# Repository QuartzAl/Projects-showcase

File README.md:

<!-- PROJECT LOGO -->
<br />
<div align="center">

<h3 align="center">Projects World!</h3>

Main repository where I keep all of my project showcases related to Electrical Engineering
These include PCB designs, electronic circuits, code snippets, and more. The directories in this repository refer to individual projects that were completed that I think do not need their own github repository

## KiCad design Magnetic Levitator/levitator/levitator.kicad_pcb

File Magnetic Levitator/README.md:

# Magnetic Levitator

A simple magnetic levitator I made with an ON-OFF controller, the system kind of Proportional controller's itself because of the inductive effect of the coil, hence why not need to use an actual proportional controller. The coil had to be wound with care as inalignment of the coil would reduce it's magnetic strength, the object to be lifted in this levitator has to also be a magnet in order to give proper feedback to the SS49E sensor. The frame of the magnetic levitator I built from several pieces of cut cardboard and hotglue, enough to hold the coil and circuit.

## Components

The main components used for the magnetic levitator is as follows:
- 2 ounces of 0.5mm diameter copper wire (around 120 Meters)
- SS49E linear hall effect sensor
- an MP1584 step down converter
- LM358 OpAmp
- IRLZ44n
- 1N5819; and
- some resistors and capacitors

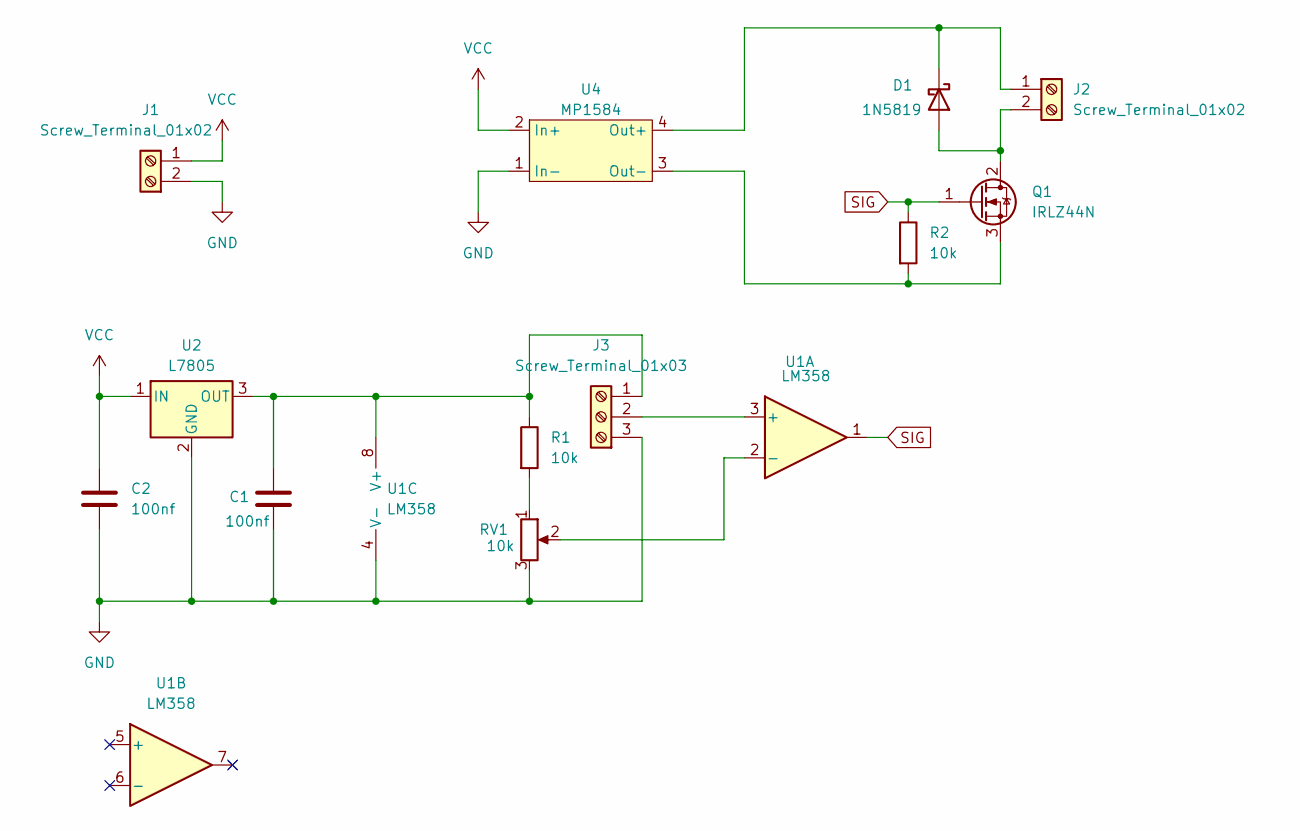
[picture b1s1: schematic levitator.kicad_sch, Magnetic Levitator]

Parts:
C1, C2: 100nf; C_1206_3216Metric_Pad1.33x1.80mm_HandSolder
D1: 1N5819; D_DO-41_SOD81_P10.16mm_Horizontal
J1: Screw_Terminal_01x02; Screw terminal
J2: Screw_Terminal_01x02; JST_EH_B2B-EH-A_1x02_P2.50mm_Vertical
J3: Screw_Terminal_01x03; JST_EH_B3B-EH-A_1x03_P2.50mm_Vertical
Q1: IRLZ44N; TO-220-3_Vertical
R1, R2: 10k; R_0805_2012Metric_Pad1.20x1.40mm_HandSolder
RV1: 10k; Potentiometer_Bourns_3296W_Vertical
U1: LM358; DIP-8_W7.62mm_LongPads
U2: L7805; TO-92_Inline_Wide
U4: MP1584

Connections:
GND: C1.2, C2.2, J1.2 (Pin_1), J3.3 (Pin_1), RV1.3, U1.4 (V-), U2.2 (GND), U4.1 (In-)
unnamed: D1.2 (A), J2.2, Q1.2 (D)
unnamed: D1.1 (K), J2.1, U4.4 (Out+)
unnamed: J3.2, U1.3 (+)
unnamed: C1.1, J3.1 (Pin_3), R1.1, U1.8 (V+), U2.3 (OUT)
unnamed: Q1.3 (S), R2.2, U4.3 (Out-)
unnamed: R1.2, RV1.1
unnamed: RV1.2, U1.2 (-)
SIG: Q1.1 (G), R2.1, U1.1
VCC: C2.1, J1.1 (Pin_2), U2.1 (IN), U4.2 (In+)

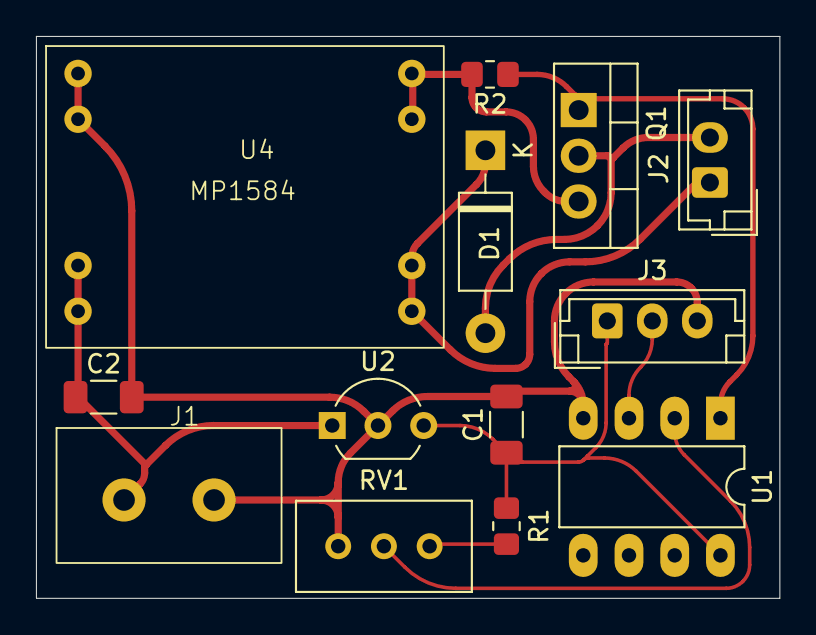
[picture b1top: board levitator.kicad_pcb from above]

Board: 2 copper layers, 41.3 x 31.2 mm, 13 parts (0 on the bottom side), 10 nets.

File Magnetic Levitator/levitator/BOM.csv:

"Reference","Value","Datasheet","Footprint","Qty","DNP"
"C1,C2","100nf","~","","2",""
"D1","1N5819","http://www.vishay.com/docs/88525/1n5817.pdf","Diode_THT:D_DO-41_SOD81_P10.16mm_Horizontal","1",""
"J1,J2","Screw_Terminal_01x02","~","","2",""
"Q1","IRLZ44N","http://www.irf.com/product-info/datasheets/data/irlz44n.pdf","Package_TO_SOT_THT:TO-220-3_Vertical","1",""
"R1,R2,RV1","10k","~","","3",""
"U1","LM358","http://www.ti.com/lit/ds/symlink/lm2904-n.pdf","","1",""
"U2","L7805","http://www.st.com/content/ccc/resource/technical/document/da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","","1",""
"U3,U4","~","","","2",""

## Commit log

2025-02-27 Add main project folders
2025-02-27 add folder
2025-02-27 change maglev readme
2025-02-28 completed description of projects
2025-02-28 add additional folder content
2025-02-28 fixed submodules
